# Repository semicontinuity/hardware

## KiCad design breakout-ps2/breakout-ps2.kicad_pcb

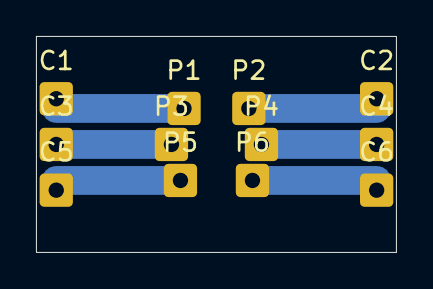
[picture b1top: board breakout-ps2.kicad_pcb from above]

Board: 2 copper layers, 20.0 x 12.0 mm, 12 parts (0 on the bottom side), 6 nets.

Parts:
C1, C2, C3, C4, C5, C6: MountingHole_Pad; SolderWire-0.25sqmm_1x01_D0.65mm_OD1.7mm
P1, P2, P3, P4, P5, P6: MountingHole_Pad; SolderWire-0.25sqmm_1x01_D0.65mm_OD1.7mm

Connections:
/CLK: C5.1, P5.1
/DATA: C1.1, P1.1
/GND: C3.1, P3.1
/RES2: C2.1, P2.1
/RES6: C6.1, P6.1
/VCC: C4.1, P4.1

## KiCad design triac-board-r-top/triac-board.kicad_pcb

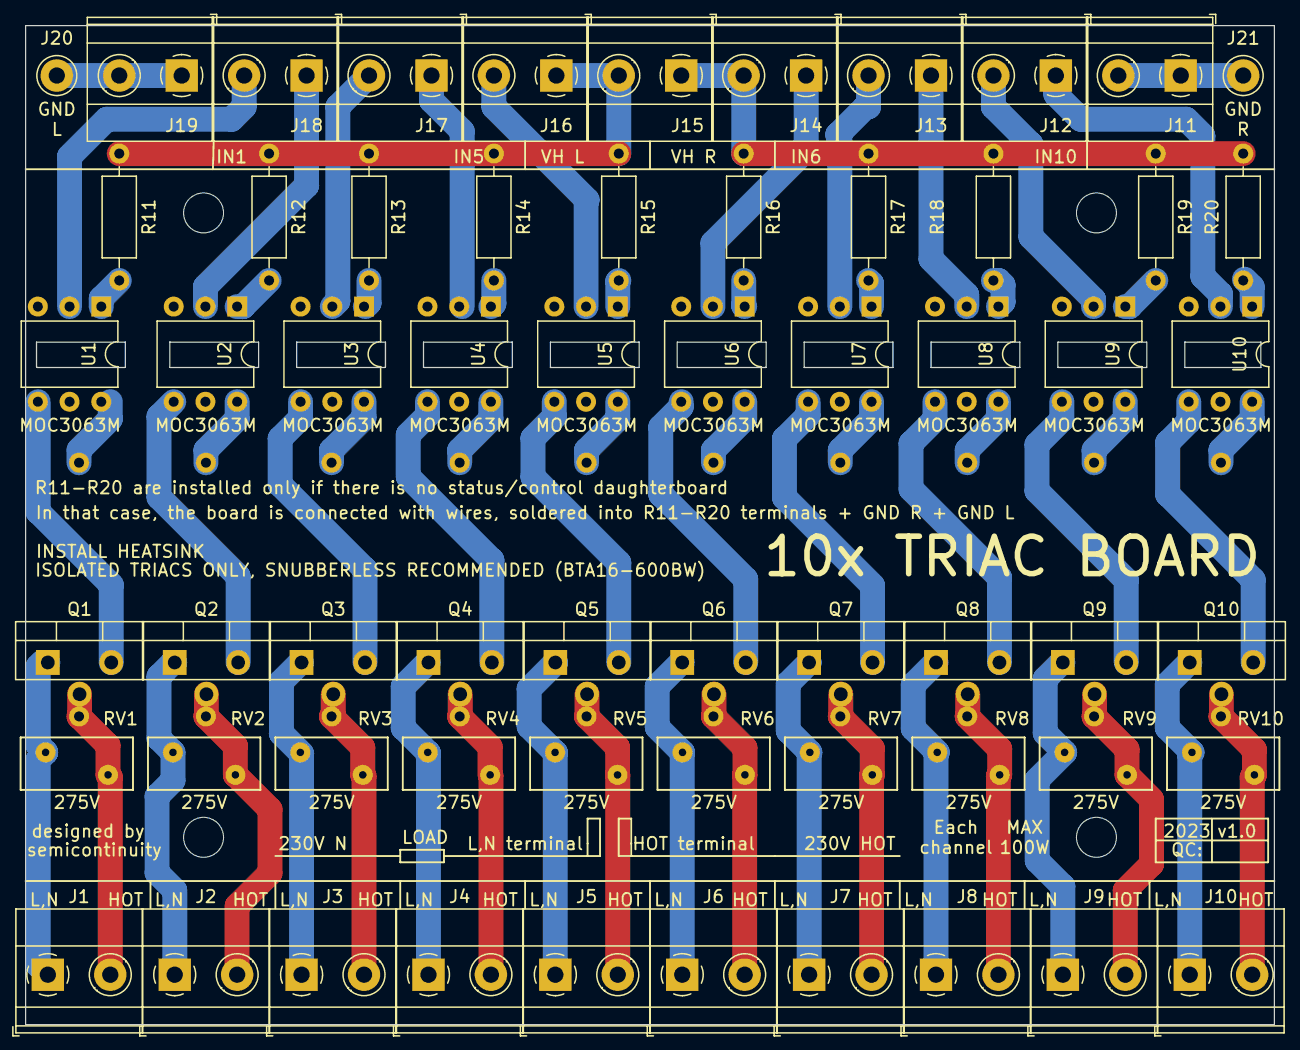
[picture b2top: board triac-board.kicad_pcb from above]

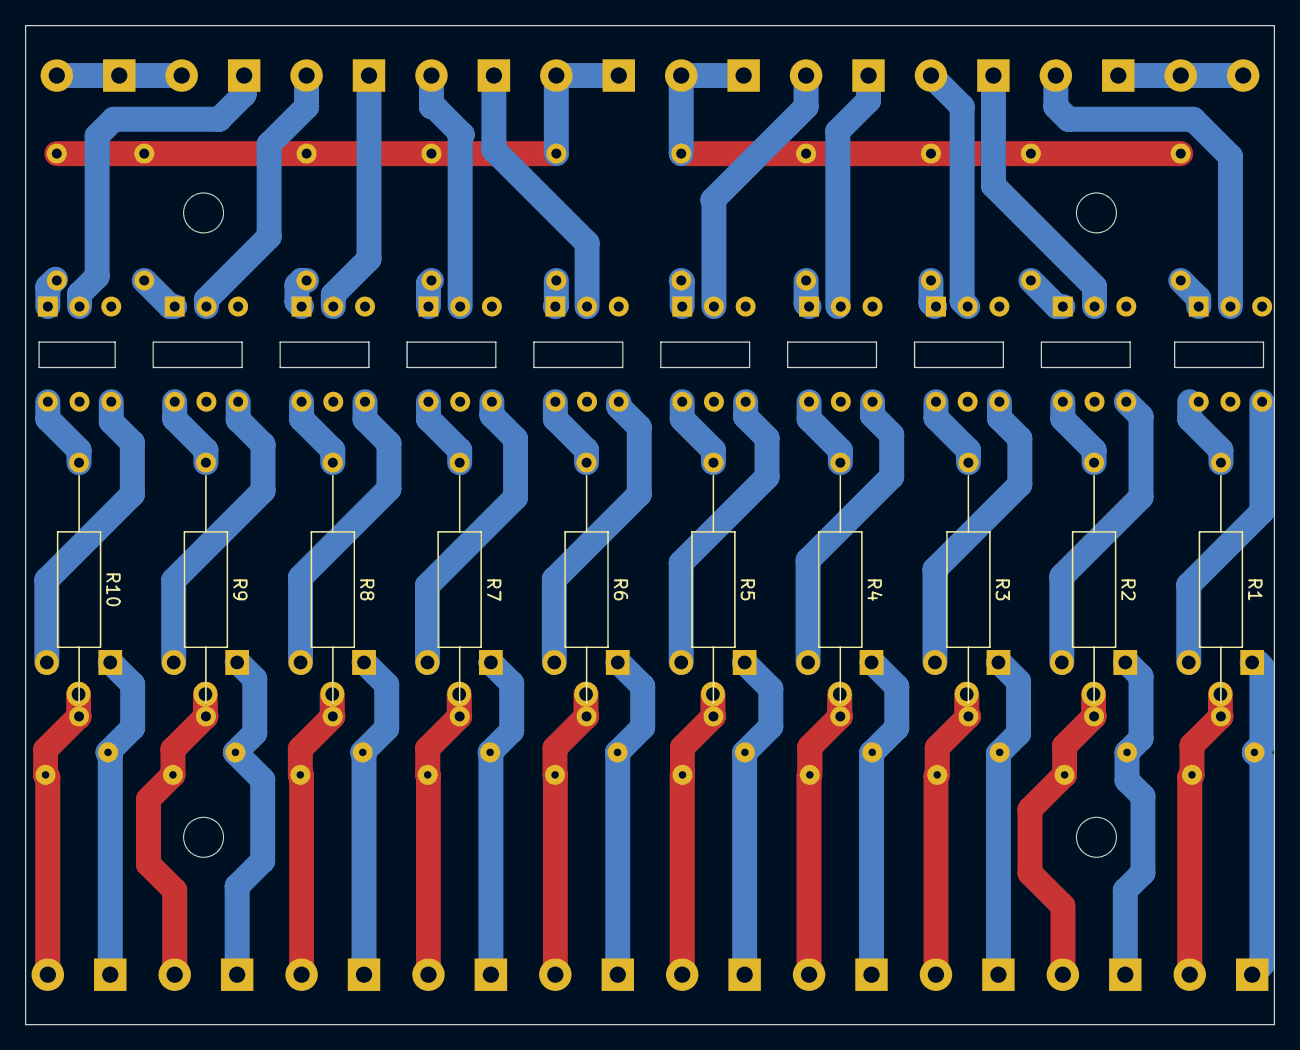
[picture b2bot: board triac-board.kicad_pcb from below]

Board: 2 copper layers, 100.0 x 80.0 mm, 75 parts (10 on the bottom side), 64 nets.

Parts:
H1, H2, H3, H4: MountingHole; MountingHole_3.2mm_M3
J1, J2, J3, J4, J5, J6, J7, J8, J9, J10, J11, J12, J13, J14, J15, J16, J17, J18, J19: Screw_Terminal_01x02; TerminalBlock_Phoenix_MKDS-1,5-2_1x02_P5.00mm_Horizontal
J20, J21: Conn_01x01_Male; Pin_D1.3mm_L11.0mm
Q1, Q2, Q3, Q4, Q5, Q6, Q7, Q8, Q9, Q10: BTA16-600BW; TO-220-3_Vertical_Staggered
R1, R2, R3, R4, R5, R6, R7, R8, R9, R10: 360 0.5W; R_Axial_DIN0309_L9.0mm_D3.2mm_P20.32mm_Horizontal
R11, R12, R13, R14, R15, R16, R17, R18, R19, R20: 1k2; R_Axial_DIN0207_L6.3mm_D2.5mm_P10.16mm_Horizontal
RV1, RV2, RV3, RV4, RV5, RV6, RV7, RV8, RV9, RV10: 275V; RV_Disc_D9mm_W4.2mm_P5mm
U1, U2, U3, U4, U5, U6, U7, U8, U9, U10: MOC3063M; DIP-6_W7.62mm

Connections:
/GND_L: J19.1, J19.2, J20.1
/GND_R: J11.1, J11.2, J21.1
/IN1: J18.2, U1.2
/IN2: J18.1, U2.2
/IN3: J17.2, U3.2
/IN4: J17.1, U4.2
/IN5: J16.2, U5.2
/IN6: J14.1, U6.2
/IN7: J13.2, U7.2
/IN8: J13.1, U8.2
/IN9: J12.2, U9.2
/IN10: J12.1, U10.2
/VH_L: J15.2, J16.1, R11.1, R12.1, R13.1, R14.1, R15.1
/VH_R: J14.2, J15.1, R16.1, R17.1, R18.1, R19.1, R20.1
unnamed: J1.1, Q1.1 (A1), RV1.2
unnamed: J1.2, Q1.2 (A2), R1.2, RV1.1
unnamed: J2.1, Q2.1 (A1), RV2.2
unnamed: J2.2, Q2.2 (A2), R2.2, RV2.1
unnamed: J3.1, Q3.1 (A1), RV3.2
unnamed: J3.2, Q3.2 (A2), R3.2, RV3.1
unnamed: J4.1, Q4.1 (A1), RV4.2
unnamed: J4.2, Q4.2 (A2), R4.2, RV4.1
unnamed: J5.1, Q5.1 (A1), RV5.2
unnamed: J5.2, Q5.2 (A2), R5.2, RV5.1
unnamed: J6.1, Q6.1 (A1), RV6.2
unnamed: J6.2, Q6.2 (A2), R6.2, RV6.1
unnamed: J7.1, Q7.1 (A1), RV7.2
unnamed: J7.2, Q7.2 (A2), R7.2, RV7.1
unnamed: J8.1, Q8.1 (A1), RV8.2
unnamed: J8.2, Q8.2 (A2), R8.2, RV8.1
unnamed: J9.1, Q9.1 (A1), RV9.2
unnamed: J9.2, Q9.2 (A2), R9.2, RV9.1
unnamed: J10.1, Q10.1 (A1), RV10.2
unnamed: J10.2, Q10.2 (A2), R10.2, RV10.1
unnamed: Q1.3 (G), U1.4
unnamed: Q2.3 (G), U2.4
unnamed: Q3.3 (G), U3.4
unnamed: Q4.3 (G), U4.4
unnamed: Q5.3 (G), U5.4
unnamed: Q6.3 (G), U6.4
unnamed: Q7.3 (G), U7.4
unnamed: Q8.3 (G), U8.4
unnamed: Q9.3 (G), U9.4
unnamed: Q10.3 (G), U10.4
unnamed: R1.1, U1.6
unnamed: R2.1, U2.6
unnamed: R3.1, U3.6
unnamed: R4.1, U4.6
unnamed: R5.1, U5.6
unnamed: R6.1, U6.6
unnamed: R7.1, U7.6
unnamed: R8.1, U8.6
unnamed: R9.1, U9.6
unnamed: R10.1, U10.6
unnamed: R11.2, U1.1
unnamed: R12.2, U2.1
unnamed: R13.2, U3.1
unnamed: R14.2, U4.1
unnamed: R15.2, U5.1
unnamed: R16.2, U6.1
unnamed: R17.2, U7.1
unnamed: R18.2, U8.1
unnamed: R19.2, U9.1
unnamed: R20.2, U10.1
